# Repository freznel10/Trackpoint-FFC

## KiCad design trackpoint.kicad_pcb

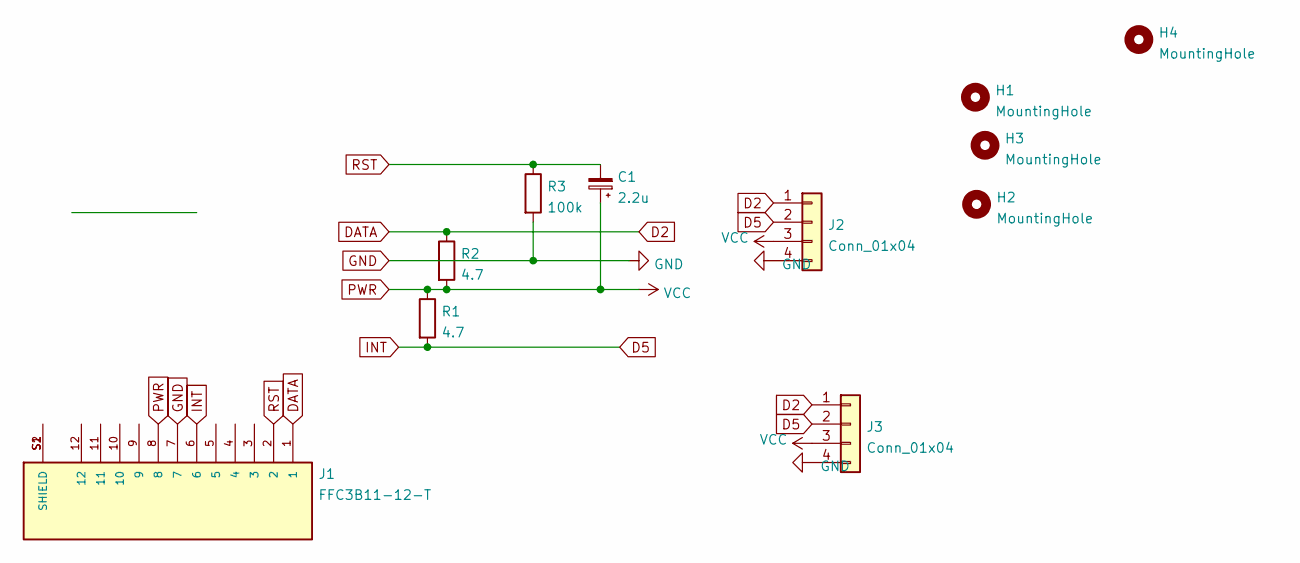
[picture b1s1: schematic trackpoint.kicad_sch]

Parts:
C1: 2.2u; C_0805_2012Metric_Pad1.18x1.45mm_HandSolder
H1, H2, H3, H4: MountingHole; MountingHole_2.2mm_M2
J1: FFC3B11-12-T; GCT_FFC3B11-12-T; PARTREV A
J2, J3: Conn_01x04; PinHeader_1x04_P2.54mm_Vertical
R1, R2: 4.7; R_0805_2012Metric_Pad1.20x1.40mm_HandSolder
R3: 100k; R_0805_2012Metric_Pad1.20x1.40mm_HandSolder

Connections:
D2: J1.1, J2.1, J3.1, R2.1
D5: J1.6, J2.2, J3.2, R1.2
GND: J1.7, J2.4, J3.4, R3.2
unnamed: J1.S1 (SHIELD), J1.S2 (SHIELD)
PWR: C1.1, J1.8, J2.3, J3.3, R1.1, R2.2
RST: C1.2, J1.2, R3.1

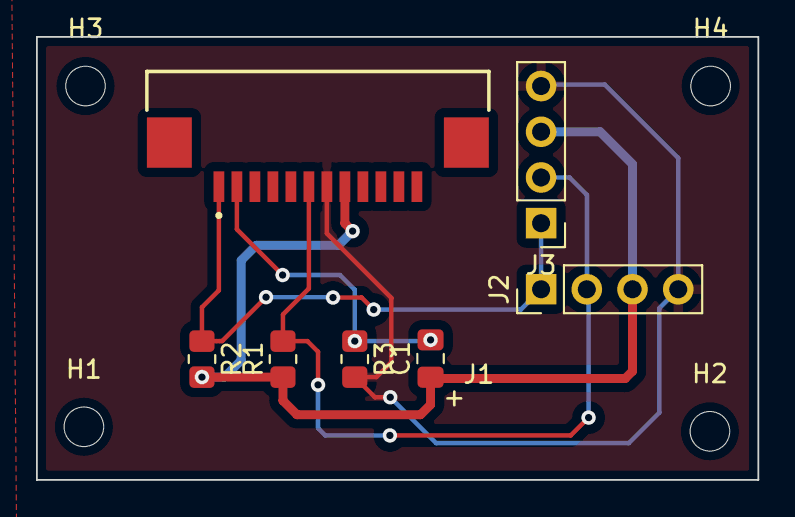
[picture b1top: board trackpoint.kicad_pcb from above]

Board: 2 copper layers, 40.1 x 24.6 mm, 11 parts (0 on the bottom side), 6 nets.

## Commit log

2022-01-09 Upload files
    Upload files
